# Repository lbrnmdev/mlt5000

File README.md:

# MLT 5000

Multicolored LED thermometer we're creatively calling the  **MLT 5000**. Purely analog functionality with temperature sensor outputting signal to two cascading display ICs

## Schema

## Creators
* F.Barraza Castillo
* E.Attah-Mensah

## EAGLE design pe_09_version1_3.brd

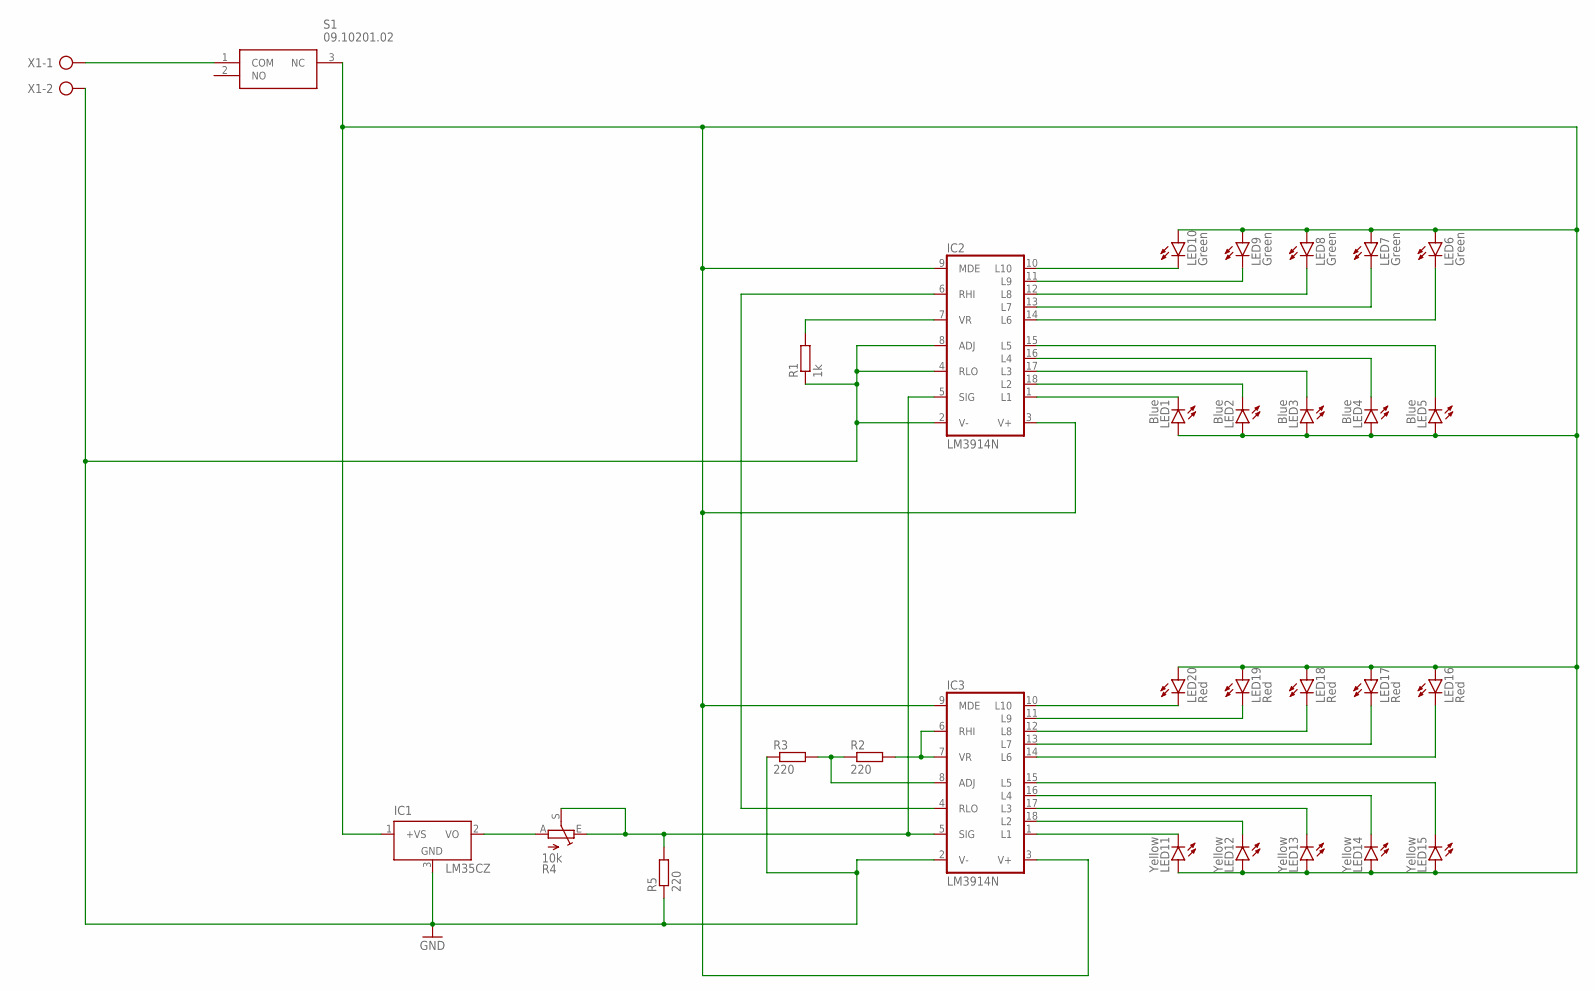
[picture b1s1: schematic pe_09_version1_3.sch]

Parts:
IC1: LM35CZ; TO92
IC2, IC3: LM3914N; DIL18
LED1, LED2, LED3, LED4, LED5: Blue; LED5MM
LED6, LED7, LED8, LED9, LED10: Green; LED5MM
LED11, LED12, LED13, LED14, LED15: Yellow; LED5MM
LED16, LED17, LED18, LED19, LED20: Red; LED5MM
R1: 1k; 0207/10
R2, R3, R5: 220; 0207/10
R4: 10k; PT-10
S1: 09.10201.02; 091020102
X1: AK500/2

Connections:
GND: IC1.3 (GND), IC2.2 (V-), IC2.4 (RLO), IC2.8 (ADJ), IC3.2 (V-), R1.1, R3.1, R5.1, X1.2
unnamed: IC2.1 (L1), LED1.K (C)
unnamed: IC2.18 (L2), LED2.K (C)
unnamed: IC2.17 (L3), LED3.K (C)
unnamed: IC2.16 (L4), LED4.K (C)
unnamed: IC2.15 (L5), LED5.K (C)
unnamed: IC2.10 (L10), LED10.K (C)
unnamed: IC2.11 (L9), LED9.K (C)
unnamed: IC2.12 (L8), LED8.K (C)
unnamed: IC2.13 (L7), LED7.K (C)
unnamed: IC2.14 (L6), LED6.K (C)
unnamed: S1.1 (COM), X1.1
unnamed: IC2.7 (VR), R1.2
unnamed: IC3.1 (L1), LED11.K (C)
unnamed: IC3.18 (L2), LED12.K (C)
unnamed: IC3.17 (L3), LED13.K (C)
unnamed: IC3.16 (L4), LED14.K (C)
unnamed: IC3.15 (L5), LED15.K (C)
unnamed: IC3.10 (L10), LED20.K (C)
unnamed: IC3.11 (L9), LED19.K (C)
unnamed: IC3.12 (L8), LED18.K (C)
unnamed: IC3.13 (L7), LED17.K (C)
unnamed: IC3.14 (L6), LED16.K (C)
unnamed: IC2.6 (RHI), IC3.4 (RLO)
unnamed: IC3.6 (RHI), IC3.7 (VR), R2.2
unnamed: IC3.8 (ADJ), R2.1, R3.2
unnamed: IC1.2 (VO), R4.A
unnamed: IC2.5 (SIG), IC3.5 (SIG), R4.E, R4.S, R5.2
V+: IC1.1 (+VS), IC2.3 (V+), IC2.9 (MDE), IC3.3 (V+), IC3.9 (MDE), LED1.A, LED2.A, LED3.A, LED4.A, LED5.A, LED6.A, LED7.A, LED8.A, LED9.A, LED10.A, LED11.A, LED12.A, LED13.A, LED14.A, LED15.A, LED16.A, LED17.A, LED18.A, LED19.A, LED20.A, S1.3 (NC)

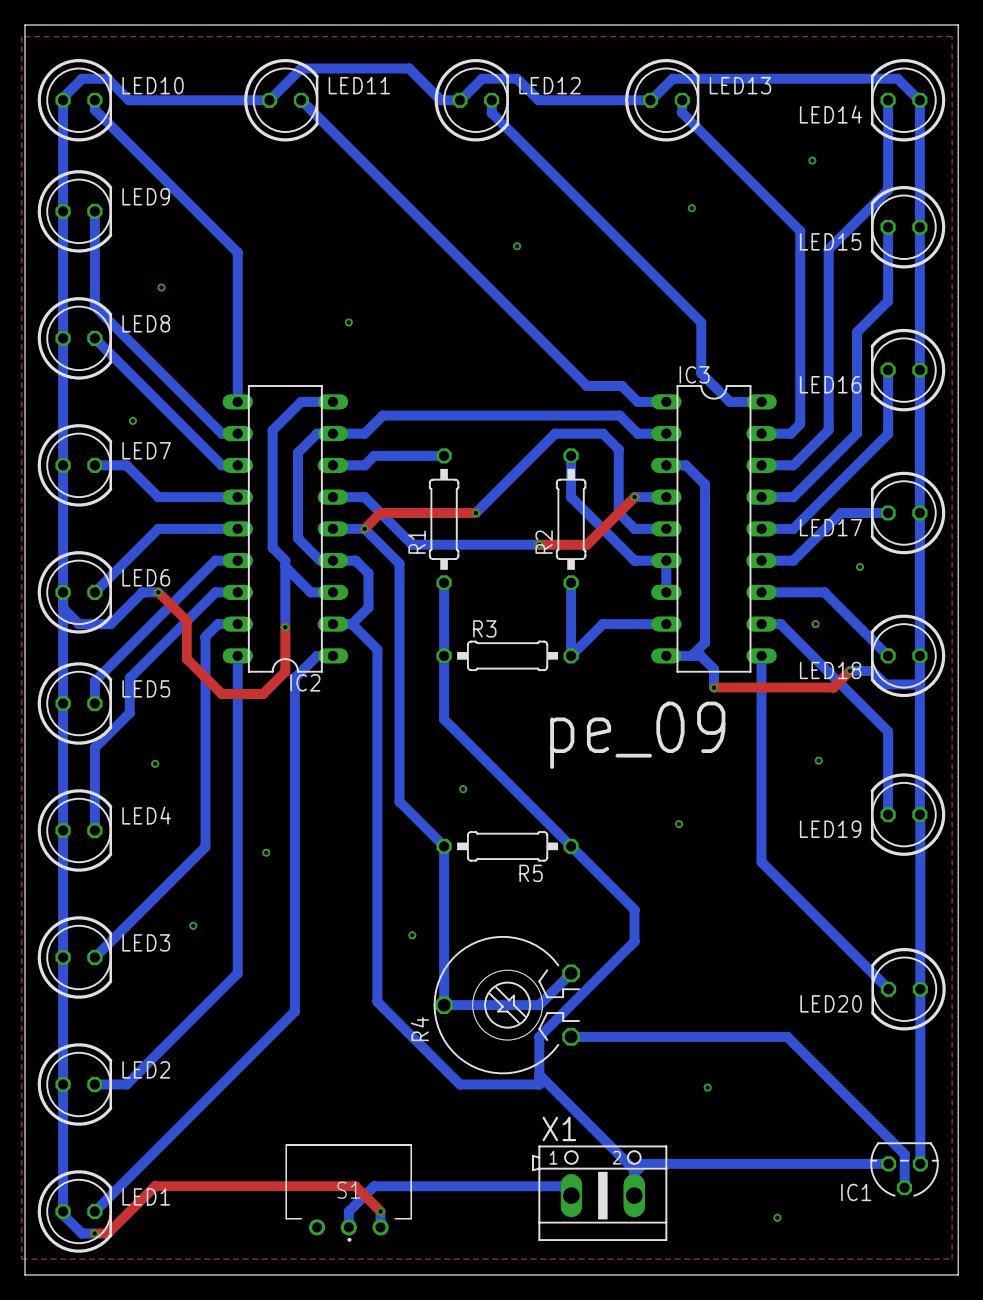
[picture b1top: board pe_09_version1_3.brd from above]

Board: 2 copper layers, 74.7 x 100.0 mm, 30 parts (0 on the bottom side), 29 nets.

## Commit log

2020-01-28 init repo
2020-01-28 fix .gitignore
2020-01-28 add readme
2020-01-28 add creators' names
2020-01-28 fix README
